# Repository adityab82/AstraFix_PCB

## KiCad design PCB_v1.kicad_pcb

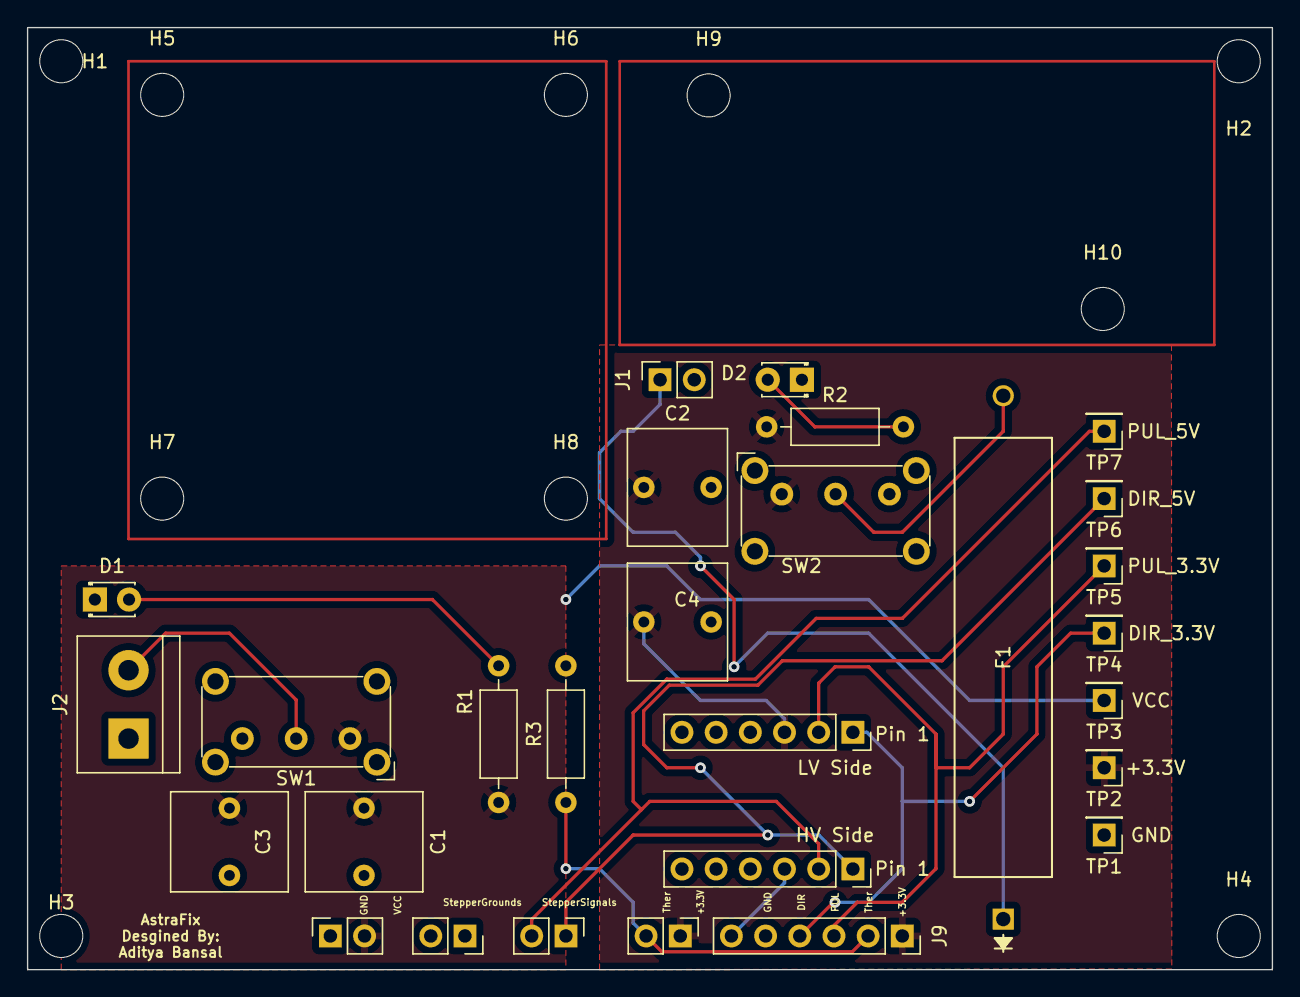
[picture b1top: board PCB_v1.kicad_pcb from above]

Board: 2 copper layers, 92.5 x 70.0 mm, 38 parts (0 on the bottom side), 14 nets.

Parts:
C1: 1000uF; C_Rect_L7.2mm_W8.5mm_P5.00mm_FKP2_FKP2_MKS2_MKP2
C2: 100uF; C_Rect_L7.2mm_W8.5mm_P5.00mm_FKP2_FKP2_MKS2_MKP2
C3, C4: 10uF; C_Rect_L7.2mm_W8.5mm_P5.00mm_FKP2_FKP2_MKS2_MKP2
D1, D2: LED; LED_D1.8mm_W3.3mm_H2.4mm
F1: Fuse; fuse_tht
H1, H2, H3, H4, H5, H6, H7, H8, H9, H10: MountingHole; MountingHole_3.2mm_M3
J1: PowerInput3.3V; PinSocket_1x02_P2.54mm_Vertical
J2: PowerInput11.1V; TerminalBlock_bornier-2_P5.08mm
J3: PowerOutput11.1V; PinSocket_1x02_P2.54mm_Vertical
J4: Thermistor; PinHeader_1x02_P2.54mm_Vertical
J5: LogicShifterIn; PinSocket_1x06_P2.54mm_Vertical
J6: LogicShifterOut; PinSocket_1x06_P2.54mm_Vertical
J7: StepperGND; PinSocket_1x02_P2.54mm_Vertical
J8: StepperSignals; PinHeader_1x02_P2.54mm_Vertical
J9: Conn_01x06_Female; PinSocket_1x06_P2.54mm_Vertical
R1, R2: 500; R_Axial_DIN0207_L6.3mm_D2.5mm_P10.16mm_Horizontal
R3: 100k; R_Axial_DIN0207_L6.3mm_D2.5mm_P10.16mm_Horizontal
SW1, SW2: SW_SPDT; SW_E-Switch_EG1224_SPDT_Angled
TP1, TP2, TP3, TP4, TP5, TP6, TP7: TestPoint; PinHeader_1x01_P2.54mm_Vertical

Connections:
+3.3V: C2.1, C4.1, J4.1, J5.3, J9.1, R2.1, SW2.1 (A), TP2.1
+5V: J6.3, J9.6
/DIR_3.3: J5.1, J9.4, TP4.1
/DIR_5: J6.1, J8.1, TP6.1
/PUL_3.3: J5.2, J9.3, TP5.1
/PUL_5: J6.2, J8.2, TP7.1
/Thermistor: J4.2, J9.2, R3.1
GND: C1.2, C2.2, C3.2, C4.2, D1.1 (K), D2.1 (K), J1.2, J2.1, J3.1, J5.4, J6.4, J7.1, J7.2, J9.5, R3.2, TP1.1
unnamed: D1.2 (A), R1.2
unnamed: D2.2 (A), R2.2
unnamed: F1.1, J1.1
unnamed: F1.2, SW2.2 (B)
unnamed: J2.2, SW1.2 (B)
VCC: C1.1, C3.1, J3.2, R1.1, SW1.1 (A), TP3.1

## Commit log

2025-02-12 working on schematic
2025-02-12 working on power circuit
2025-03-16 schematic done
2025-03-16 schematic updated
2025-03-17 added footprints and layout
2025-03-20 completed PCB
2025-03-20 output files generated
